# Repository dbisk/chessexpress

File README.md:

# The Chess Express

The Chess Express, an Automatic Chessboard inspired by Wizard's Chess from _Harry Potter and the Sorcerer's Stone_

Unfortunately, our implementation does not destroy the pieces like true wizard chess, but perhaps we can make a definitely not OSHA-compliant addon for that :P. (exploding capacitors, anyone?)

Hermoine doesn't approve.

## Repository Layout

The repository is laid out as follows:

1. `src` holds the source code for the programming both onto the LPC1114/102 FN28 processor, as well as a python program (in the works) that interfaces with the LPC code via serial.

2. `hardware` holds the hardware design files and documentation. See this if you are looking to reproduce the hardware rig made for this project.

3. `doc` holds high-level documentation as well as a full lab report for the project. See the README in the `doc` folder for the lab report.

## Usage

Assuming you have the rig completely set up (if not, see the next section for details), you can start up the python program to interface with the chessboard simply with
```
python chessexpress.py --port COM5
```
in the _____ folder.

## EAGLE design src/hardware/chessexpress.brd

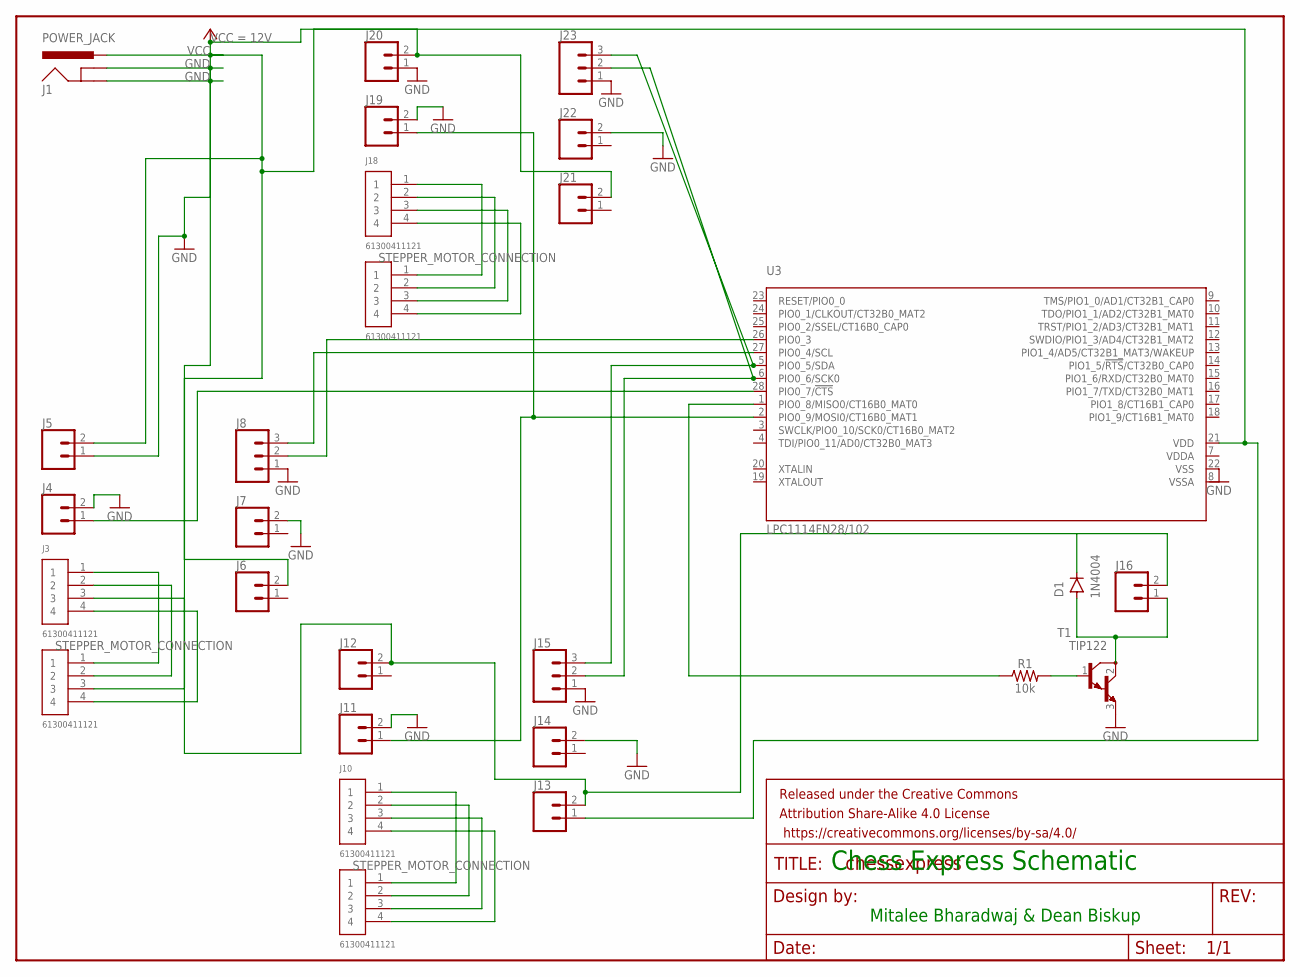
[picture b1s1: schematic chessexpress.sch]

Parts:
D1: 1N4004; DO-41
FRAME: FRAME-LETTERNO_PACKAGE; DUMMY
J1: POWER_JACK; POWER_JACK_PTH
J2, J3, J9, J10, J17, J18: 61300411121
J4, J5, J6, J7, J11, J12, J13, J14, J16, J19, J20, J21, J22: CONN_02; 1X02
J8, J15, J23: CONN_03; 1X03
R1: 10k; 0603
T1: TIP122; TO220
U3: LPC1114FN28/102; SOT117

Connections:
GND: J1.GND, J1.GNDBREAK, J4.2, J5.1, J7.2, J8.1, J11.2, J14.2, J15.1, J19.2, J20.1, J22.2, J23.1, T1.3 (E), U3.22 (VSS)
J2_1: J2.1, J3.1
J2_2: J2.2, J3.2
J2_3: J2.3, J3.3
J2_4: J2.4, J3.4
J2_5: J9.1, J10.1
J2_6: J9.2, J10.2
J2_7: J9.3, J10.3
J2_8: J9.4, J10.4
J2_9: J17.1, J18.1
J2_10: J17.2, J18.2
J2_11: J17.3, J18.3
J2_12: J17.4, J18.4
unnamed: J4.1, U3.28 (PIO0_7/!CTS!)
unnamed: D1.A, J16.1, T1.2 (C)
unnamed: J11.1, J19.1, U3.2 (PIO0_9/MOSI0/CT16B0_MAT1)
unnamed: J8.3, U3.27 (PIO0_4/SCL)
unnamed: J8.2, U3.26 (PIO0_3)
unnamed: R1.1, U3.1 (PIO0_8/MISO0/CT16B0_MAT0)
unnamed: R1.2, T1.1 (B)
unnamed: J15.3, J23.3, U3.5 (PIO0_5/SDA)
unnamed: J15.2, J23.2, U3.6 (PIO0_6/SCK0)
VCC: D1.C, J1.PWR, J5.2, J6.2, J12.2, J13.1, J13.2, J16.2, J20.2, J21.2, U3.21 (VDD)
VDDA: U3.7 (VDDA)
VSSA: U3.8 (VSSA)

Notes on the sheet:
Chess Express Schematic
Mitalee Bharadwaj & Dean Biskup

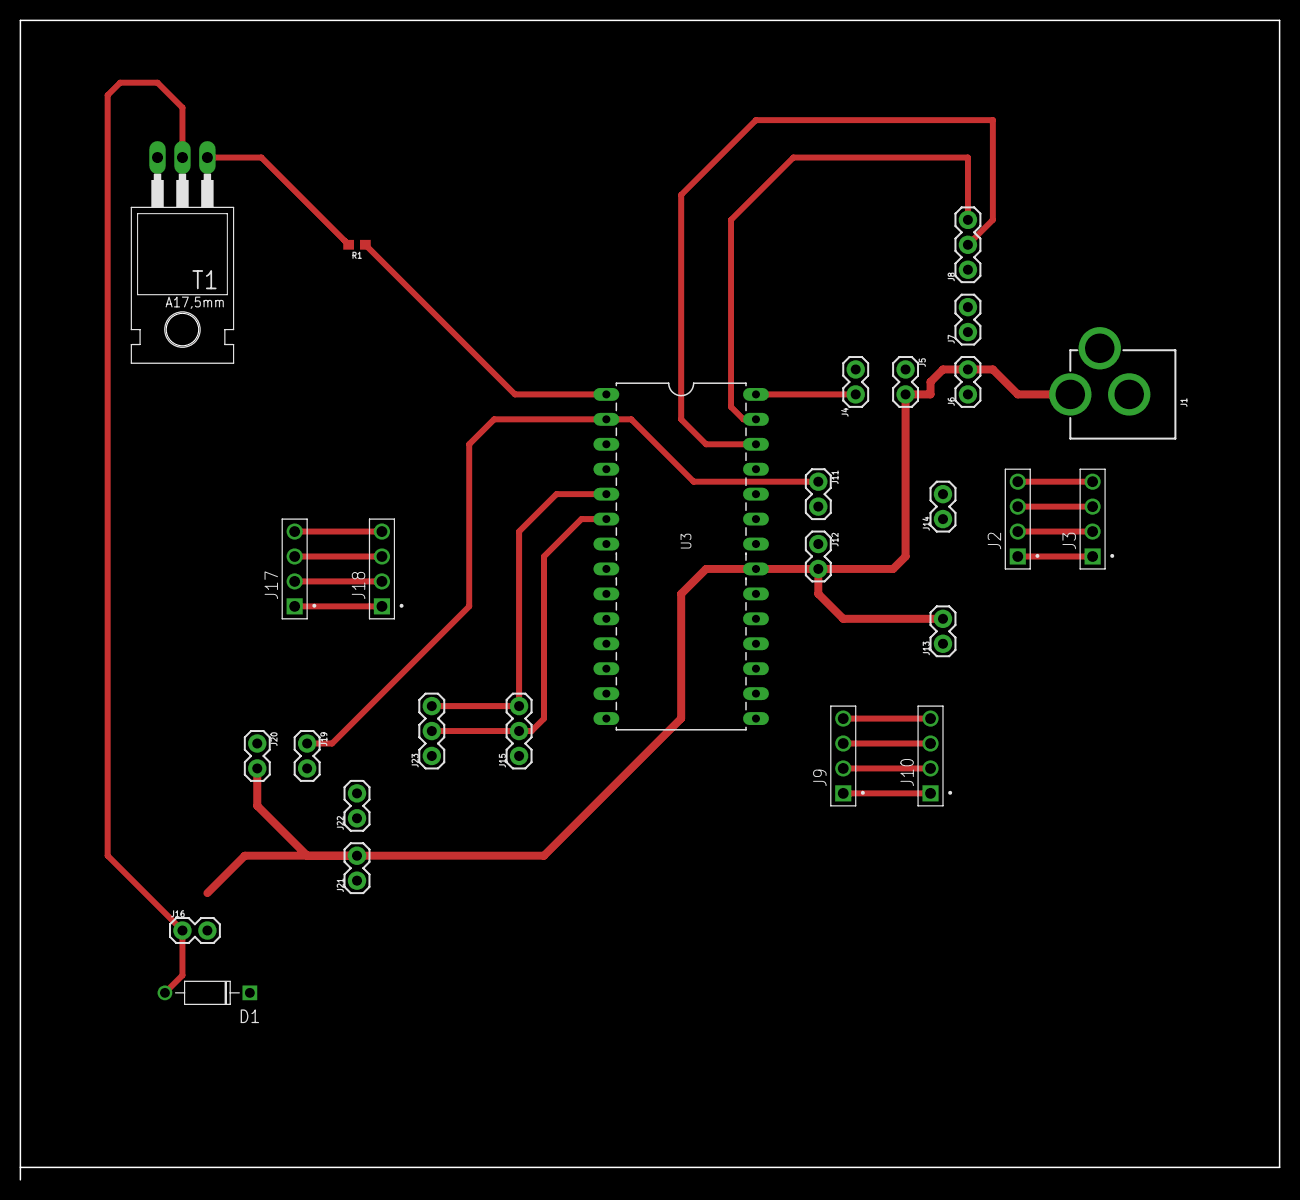
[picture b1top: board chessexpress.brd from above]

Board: 2 copper layers, 128.3 x 118.1 mm, 28 parts (0 on the bottom side), 23 nets.

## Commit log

2019-09-24 Added doc files
2019-09-25 rebase
2019-10-02 Added lpc21isp submodule
2019-10-10 Functions for chessboard logic. No implementations for pawn moves or range bounding, but a scripted chess game should be handled.
2019-10-13 Added uvision files and updated gitignore to handle uvision temp files
2019-10-13 Set up structures for controlling 2 axes in MCU. Restructured project for use with uVision.
2019-10-14 Added mcu.c, with some implementations
2019-10-18 testing changes. seemed like issue was time wait between steps too small for full steps. 8th steps ok.
2019-10-18 Testing multiple calls of moveMotor. Also updated resetEDPins to be more modular.
2019-10-18 Changed pinning on the processor for motors. Cleaned up testing sequence. Removed MS1 and MS2 pins from processor. Assuming full step on motors now.
2019-10-18 Added moveMotor infinitely functionality for 1 axis
2019-10-18 updated pins for GPIO1
2019-10-20 Serial works at least to scan and print. Workaround for weird bug where first scanned character was decremented by 1.
2019-10-20 Added conversion to uppercase for passed in serial moves
2019-10-27 Added initial game files. Needs work
2019-10-27 Updated testing sequence, removed warnings, and added graveyard logic.
2019-10-27 Fixed compile errors. Fixed stack overflow issues. Looks like we can't have a full representation of the board + printf call, or also can't have 2 full representations of the board. The stack is real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
2019-11-07 Documentation updates for MCU
2019-11-07 Draft for Electromagnet section, without images
2019-11-08 Moved pin assignments around to make both Y and X axes work
2019-11-15 Added some documentation
2019-11-15 Added issue templates
2019-11-19 (#6) Added initial python files
2019-11-20 (#6) Added game logic and loop. Also added better debug output.
2019-11-20 (#6) Added lpc-comm functions, but needs testing
2019-12-11 (#7) Remove game logic from C code. Python program works with C-code, but does not restrict illegal chess moves.
2019-12-11 (#7) Bugfix for Python program to wait for an additional ACK from the MCU
2019-12-17 Added hardware files
2019-12-17 (#10) Finished documentation/ lab report
2019-12-19 (18) Added requirements.txt
2020-02-10 Add feature request issue template
2020-03-03 Added block diagram
2020-03-04 Updated block diagram
2020-03-04 Directory restructuring
2020-03-04 gitignore ignores python virtual environments
2020-03-04 (#27) Added some starter code for CircuitPython
2020-03-09 adding some files, but should rebase this commit
2020-03-09 Added some empty files to be built upon

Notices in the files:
parts and their libraries:
SparkFun-Aesthetics: Licensing: Creative Commons ShareAlike 4.0 International - https://creativecommons.org/licenses/by-sa/4.0
SparkFun-Aesthetics: Released under the Creative Commons Attribution Share-Alike 4.0 License
SparkFun-Aesthetics: https://creativecommons.org/licenses/by-sa/4.0
